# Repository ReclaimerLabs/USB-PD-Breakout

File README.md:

# Introduction

This board features an FUSB302B as a Type-C Port Management (TCPM) chip. You can purchase one on [Tindie](https://www.tindie.com/products/ReclaimerLabs/usb-type-c-power-delivery-phy-breakout-board/). 

# Features

The FUSB302B is a fully-capable USB Power Delivery device. The power header is rated to 100 W (20 V at 5 A) if both Vbus pins are used along with two ground pins. The FUSB302B's max I2C clock frequency is 1 MHz. 

# Example Usage

Example code for use with Arduino can be found [here](https://github.com/graycatlabs/usb-c-arduino/tree/master/usb-c-demo). The [USB-C Explorer](https://github.com/ReclaimerLabs/USB-C-Explorer/tree/master/firmware/USB-C%20Explorer) also uses the same chip. 

Here are the connections you will need. 

* Breakout Pin -> Arduino Pin
* GND -> GND
* Vbus -> Vin (power to the Arduino, regulated down to +5V)
* Vpu -> IOREF (power for pullups for I2C and interrupt)
* VDD -> 3.3V (power for the FUSB302B)
* SDA -> SDA
* SCL -> SCL
* INT -> D12
* GND -> GND (for good measure)

# Questions, Comments, and Contributions

Pull requests are welcome. If you have questions or comments, you can email me directly at jason@reclaimerlabs.com.

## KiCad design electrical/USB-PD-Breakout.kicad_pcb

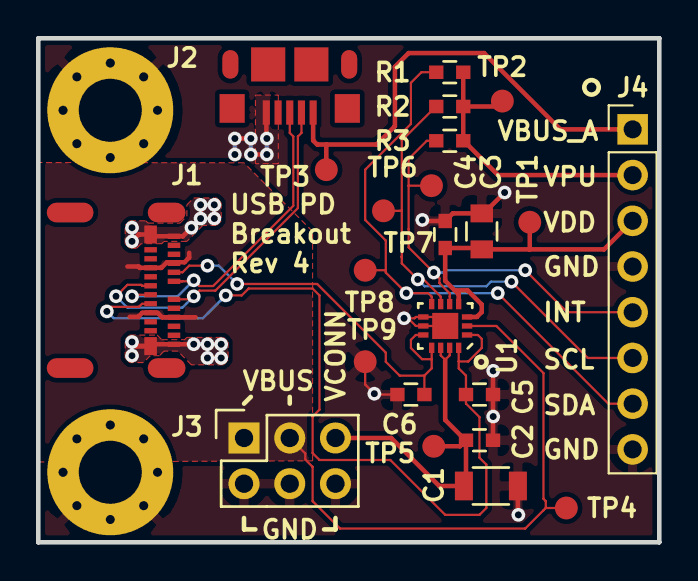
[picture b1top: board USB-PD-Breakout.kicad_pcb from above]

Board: 2 copper layers, 34.5 x 28.0 mm, 25 parts (0 on the bottom side), 13 nets.

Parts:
C1: 10uF; C_1206
C2, C4: 0.1uF; C_0603
C3: 1uF; C_0805
C5, C6: 470pF; C_0603
J1: USB-C_Female; USB-C_Female_105450-0101
J2: USB_OTG; USB_Micro-B_10118193
J3: CONN_02X03; Socket_Strip_Straight_2x03
J4: Conn_01x08_Male; Socket_Strip_Straight_1x08_Pitch2.54mm
R1, R2, R3: 4.7k; C_0603
TP1, TP2, TP3, TP4, TP5, TP6, TP7, TP8, TP9: TEST_1P; TP
U1: FUSB302BMPX; MLP_14
X1, X2: MTHOLE; MountingHole_3.5mm_Pad_Via

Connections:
/SCL: J4.6, R2.2, TP7.1, U1.6
/SDA: J4.7, R1.2, TP8.1, U1.7
/USB20_D+: J1.A6, J1.B6, J2.3
/USB20_D-: J1.A7, J1.B7, J2.2
/USBC_CC1: C6.1, J1.A5, U1.10, U1.11
/USBC_CC2: C5.1, J1.B5, U1.1, U1.14
/~INT: J4.5, R3.2, TP6.1, U1.5
GND: C1.2, C2.2, C3.2, C4.2, C5.2, C6.2, J1.A1, J1.A12, J1.B1, J1.B12, J2.5, J3.2, J3.4, J3.6, J4.4, J4.8, TP9.1, U1.8, U1.9, U1.15, X1.1, X2.1
VBUS_A: J2.1, J4.1, TP3.1
VBUS_C: J1.A4, J1.A9, J1.B4, J1.B9, J3.1, J3.3, TP4.1, U1.2
VCONN: C1.1, C2.1, J3.5, TP5.1, U1.12, U1.13
VDD: C3.1, C4.1, J4.3, TP1.1, U1.3, U1.4
V_PULLUP: J4.2, R1.1, R2.1, R3.1, TP2.1

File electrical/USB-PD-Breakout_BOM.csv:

Reference, Value, Footprint, Datasheet, Manufacturer, Manufacturer Part Number, Supplier 1, Supplier 1 Part Number, MacroFab Part Number
J1,USB-C_Female,Reclaimer_Labs:USB-C_Female_105450-0101,,JAE Electronics,DX07S024JJ3R1300,Digikey,670-2846-1-ND,
R1,4.7k,Capacitors_SMD:C_0603,,Yageo,RC0805FR-074K7L,Digikey,311-4.70KCRCT-ND,MF-RES-0603-4.7K
C5,470pF,Capacitors_SMD:C_0603,,Yageo,CC0603KRX7R9BB471,Digikey,311-1078-1-ND,
C3,1uF,Capacitors_SMD:C_0805,,,,,,MF-CAP-0805-1uF
C2,0.1uF,Capacitors_SMD:C_0603,,,,,,MF-CAP-0603-0.1uF
C1,10uF,Capacitors_SMD:C_1206,,,,,,MF-CAP-1206-10uF
C6,470pF,Capacitors_SMD:C_0603,,Yageo,CC0603KRX7R9BB471,Digikey,311-1078-1-ND,
R2,4.7k,Capacitors_SMD:C_0603,,Yageo,RC0805FR-074K7L,Digikey,311-4.70KCRCT-ND,MF-RES-0603-4.7K
R3,4.7k,Capacitors_SMD:C_0603,,Yageo,RC0805FR-074K7L,Digikey,311-4.70KCRCT-ND,MF-RES-0603-4.7K
U1,FUSB302BMPX,Reclaimer_Labs:MLP_14,,Fairchild,FUSB302BMPX,Digikey,FUSB302BMPXCT-ND,
C4,0.1uF,Capacitors_SMD:C_0603,,,,,,MF-CAP-0603-0.1uF
J2,USB_OTG,Reclaimer_Labs:USB_Micro-B_10118193,,,,,,MF-CON-MICROUSB-RIGHT
J4,CONN_02X03,Socket_Strips:Socket_Strip_Angled_2x03,,,,,,MF-CON-2.54mm-2x3
J3,CONN_02X03,Socket_Strips:Socket_Strip_Angled_2x03,,,,,,MF-CON-2.54mm-2x3
J5,CONN_02X03,Socket_Strips:Socket_Strip_Angled_2x03,,,,,,MF-CON-2.54mm-2x3

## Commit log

2016-04-30 :octocat: Added .gitattributes
2016-04-30 Version 1
    Rev 1 sent to fab
2016-12-24 Updated drl file
    Had to merge the drl files together to accomadate Macrofab
2017-04-19 Rev2 Update
2018-08-07 added readme
2018-08-07 added license file
2019-07-22 Rev 4
    Final Rev 4 design. Simplied headers, shrank board area, and added testpoints for DFM.
